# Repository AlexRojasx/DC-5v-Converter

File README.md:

<h1>DC/DC-5v-Converter</h1>

<h2>Project Description:</h2>

The DC/DC 5v converter project is aimed to create a simple and easy way to power a usb device. The primary focus was for this device to be able to power an Orange Pi off of a Rev Robotics PDH (Power Distribution Hub) for simple integration in a FRC Robot. This simple PCB board design was used to deepen my understanding of circit design, PCB layout, and PCB manufacturing.

<h2>Skills Learned:</h2>

-PCB Design and Layout  
-How to Utilize Bypass Capacitors  
-Understanding of component selection  
-PCB Manufacturing

<h2>Tools Used:</h2>

-Kicad for PCB Layout and Design  
-Reflow Oven
-Soldering Iron
-Oscilloscope for analyzing noise and PCB trobleshooting  

<h2>Screenshots:</h2>

<b>Schematic:</b>

The circit utilized a LM340s-5.0 fixed power regulator, which required a custom symbol and footprint to be made. The LM340 requires a 0.22uF bypass capacitor to filter any noise that could be caused from external influences, as well as a Schottky diode for reverse polarity protection.

<b>PCB Layout:</b>

For the layout, I utilized copper pours connected to ground on both sides for an easy and accesible ground referance and to minimize any possible noise. The traces are also wide enough to handle the 0.5 amps of current at either 12v or 5v. The bypass capacitors are placed in close proximity to the IC to reduce as much noise as possible.

<b>PCB Assembly:</b>

For the assembly of the PCB I used PCBWay to manufacture the empty circut board while I ordered the parts seperatly of off Mouser. Utilizing an Infared reflow oven, I assembled the SMD components on the PCB and hand soldering for the through hole components.

<h2>What Could be Improved:</h2>

While the PCB is small, compact and is an overall improvement from the buck converters with its ease of use that the Frc team was using, there were a couple problems. One of the main problems was the heat dissipation of the PCB and the lack of heat sinks used causing the board to become very hot risking damage to some of the components if used for a sustained period of time. This problem is easily fixable with either the use of a proper heat sink or increasing the size of the board and ground pours for the PCB to act as a heat sink. Another problem was the lack of mounting holes, making it diffucult to build a secure case or mount the pcb securely to the robot. Mounting hole can be added to the pcb but it would most likely cause the board to be slightly bigger than it is now.

<h2>Datasheets:</h2>

Ti LM340s-5v Voltage regulator: https://www.ti.com/lit/ds/symlink/lm340.pdf

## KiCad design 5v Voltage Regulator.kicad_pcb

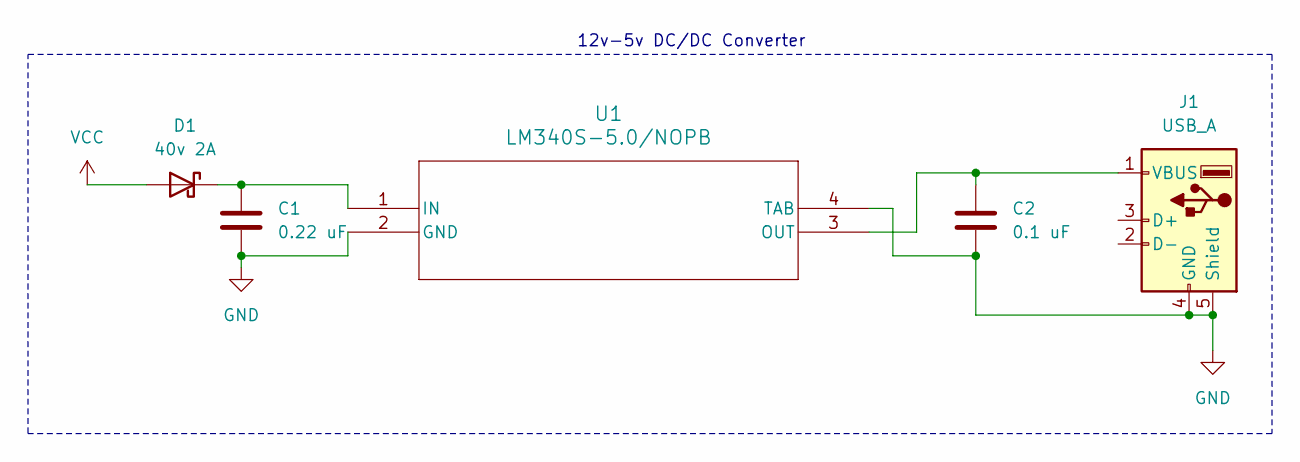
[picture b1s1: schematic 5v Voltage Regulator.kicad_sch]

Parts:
C1: 0.22 uF; C_1206_3216Metric
C2: 0.1 uF; C_1206_3216Metric
D1: 40v 2A; D_1206_3216Metric
J1: USB_A; USB_A_Molex_67643_Horizontal
U1: LM340S-5.0/NOPB; TS3B_TEX

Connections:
GND: C1.2, C2.2, J1.4 (GND), J1.5 (Shield), U1.2 (GND), U1.4 (TAB)
unnamed: C1.1, D1.1 (K), U1.1 (IN)
unnamed: C2.1, J1.1 (VBUS), U1.3 (OUT)
VCC: D1.2 (A)

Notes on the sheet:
12v-5v DC/DC Converter

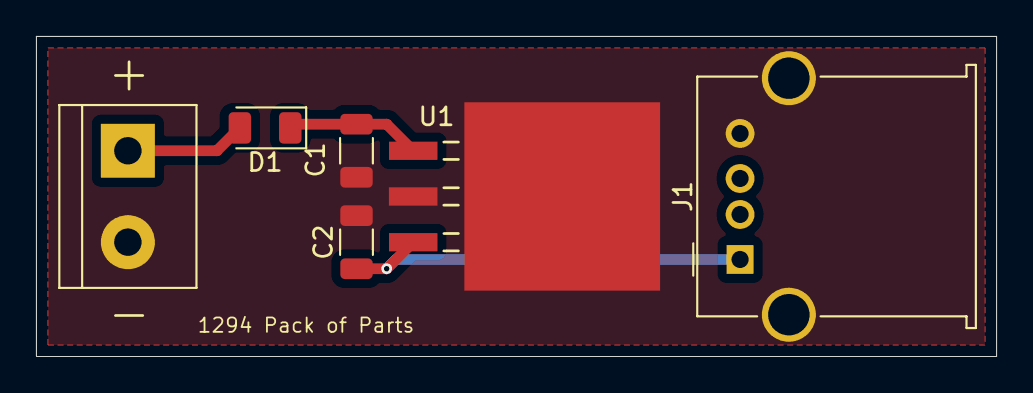
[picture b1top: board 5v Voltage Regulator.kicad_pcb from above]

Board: 2 copper layers, 53.3 x 17.8 mm, 5 parts (0 on the bottom side), 3 nets.
